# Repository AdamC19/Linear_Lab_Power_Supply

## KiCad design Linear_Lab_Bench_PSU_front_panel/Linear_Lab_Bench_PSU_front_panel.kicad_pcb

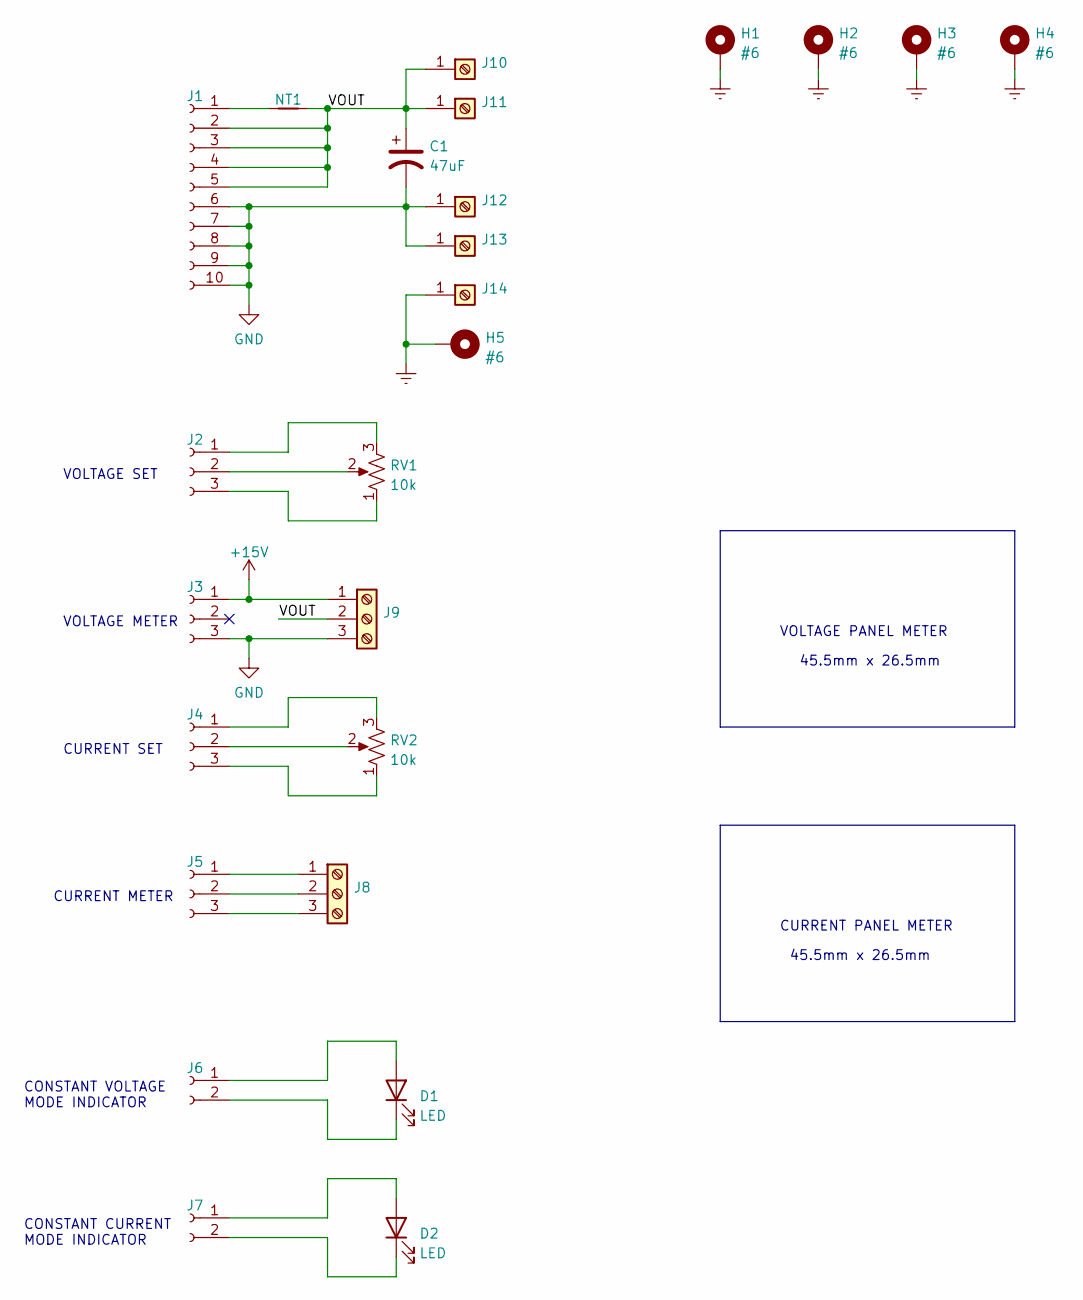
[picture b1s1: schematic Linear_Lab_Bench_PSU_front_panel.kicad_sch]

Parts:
C1: 47uF; CP_Radial_D8.0mm_P3.50mm
D1, D2: LED; LED_D5.0mm
H1, H2, H3, H4, H5: #6; MountingHole_3.7mm_Pad
J1: Conn_01x10_Female; PinSocket_1x10_P2.54mm_Vertical
J2, J3, J4, J5: Conn_01x03_Female; PinSocket_1x03_P2.54mm_Vertical
J6, J7: Conn_01x02_Female; PinSocket_1x02_P2.54mm_Vertical
J8, J9: Screw_Terminal_01x03; PhoenixContact_MCV_1,5_3-G-3.81_1x03_P3.81mm_Vertical
J10, J11, J12, J13, J14: Screw_Terminal_01x01; MountingHole_5.3mm_M5_Pad_Via
NT1: NetTie_2; NetTie-2_SMD_Pad0.5mm
RV1, RV2: 10k; Pot_TT_P160KNPD-4FC

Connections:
+15V: J3.1, J9.1
/VOUT: C1.1, J1.2, J1.3, J1.4, J1.5, J9.2, J10.1, J11.1, NT1.2
Earth: H1.1, H2.1, H3.1, H4.1, H5.1, J14.1
GND: C1.2, J1.6, J1.7, J1.8, J1.9, J1.10, J3.3, J9.3, J12.1, J13.1
unnamed: D1.1 (K), J6.2
unnamed: D1.2 (A), J6.1
unnamed: D2.1 (K), J7.2
unnamed: D2.2 (A), J7.1
unnamed: J1.1, NT1.1
unnamed: J2.1, RV1.3
unnamed: J2.2, RV1.2
unnamed: J2.3, RV1.1
unnamed: J4.1, RV2.3
unnamed: J4.2, RV2.2
unnamed: J4.3, RV2.1
unnamed: J5.1, J8.1
unnamed: J5.2, J8.2
unnamed: J5.3, J8.3

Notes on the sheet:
45.5mm x 26.5mm
VOLTAGE METER
CURRENT PANEL METER
CURRENT METER
VOLTAGE PANEL METER
CONSTANT CURRENT MODE INDICATOR
CURRENT SET
VOLTAGE SET
CONSTANT VOLTAGE MODE INDICATOR

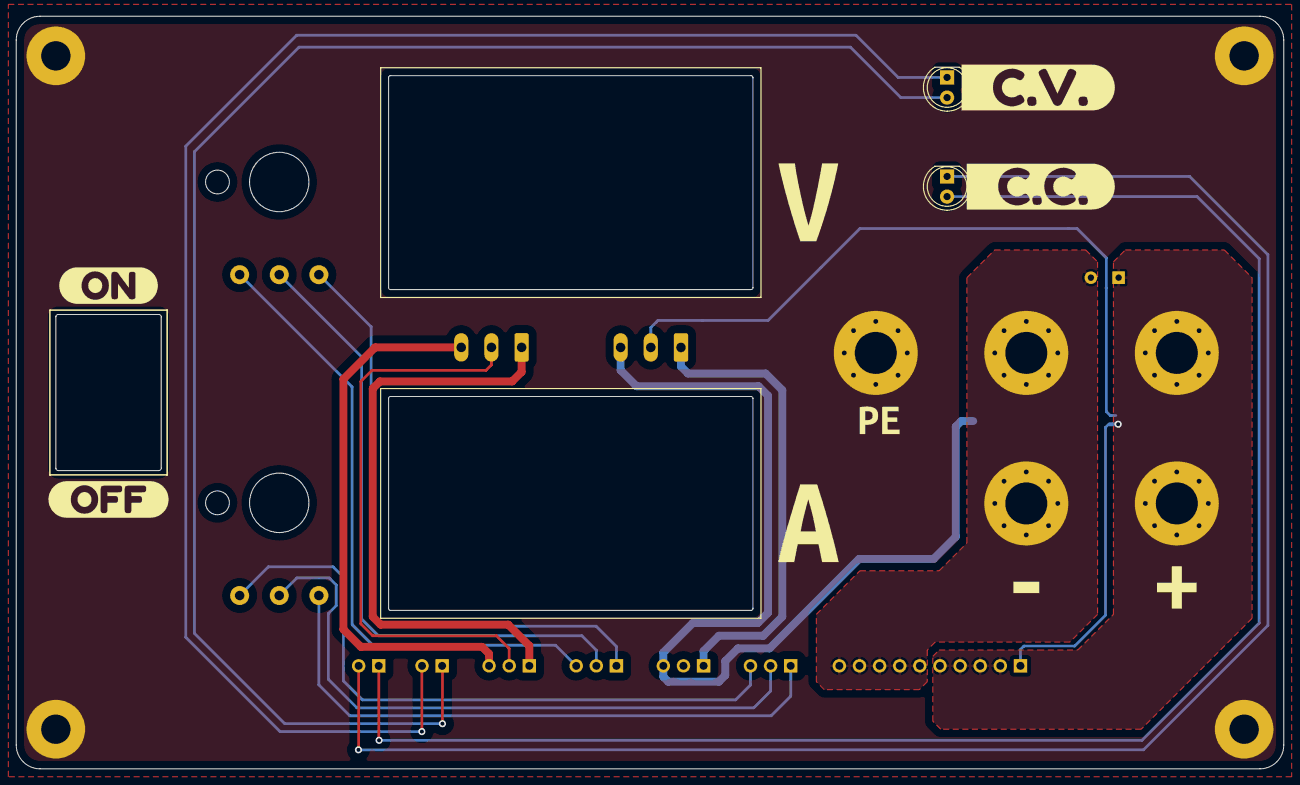
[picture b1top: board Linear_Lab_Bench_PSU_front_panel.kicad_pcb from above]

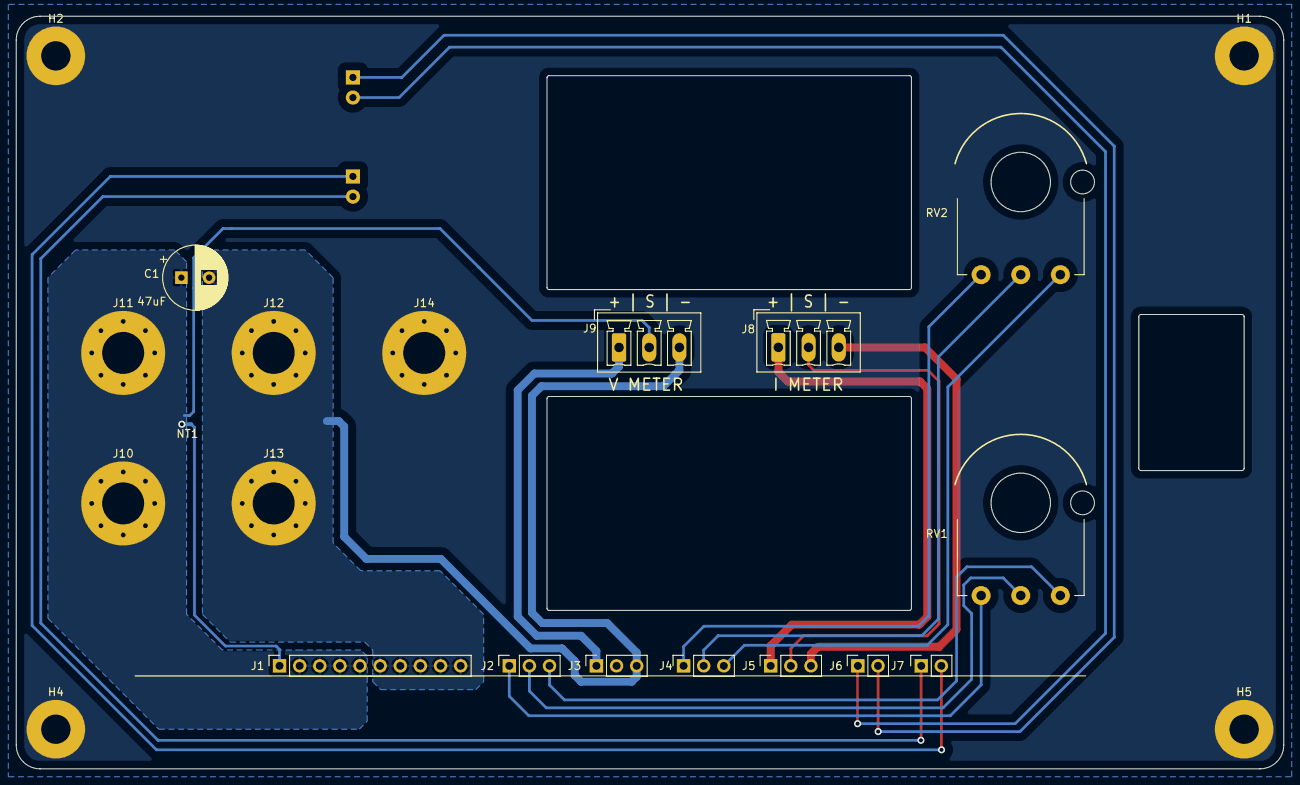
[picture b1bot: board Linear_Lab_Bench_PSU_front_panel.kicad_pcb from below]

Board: 2 copper layers, 160.0 x 95.0 mm, 33 parts (22 on the bottom side), 18 nets.

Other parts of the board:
kibuzzard-6225A7BC: G***; kibuzzard-6225A7BC
kibuzzard-6225A7C7: G***; kibuzzard-6225A7C7
kibuzzard-6225A77E: G***; kibuzzard-6225A77E
kibuzzard-6225A745: G***; kibuzzard-6225A745
kibuzzard-6225A755: G***; kibuzzard-6225A755
kibuzzard-62263B3C: G***; kibuzzard-62263B3C
kibuzzard-62263B33: G***; kibuzzard-62263B33
kibuzzard-62263C4A: G***; kibuzzard-62263C4A
kibuzzard-62263C42: G***; kibuzzard-62263C42

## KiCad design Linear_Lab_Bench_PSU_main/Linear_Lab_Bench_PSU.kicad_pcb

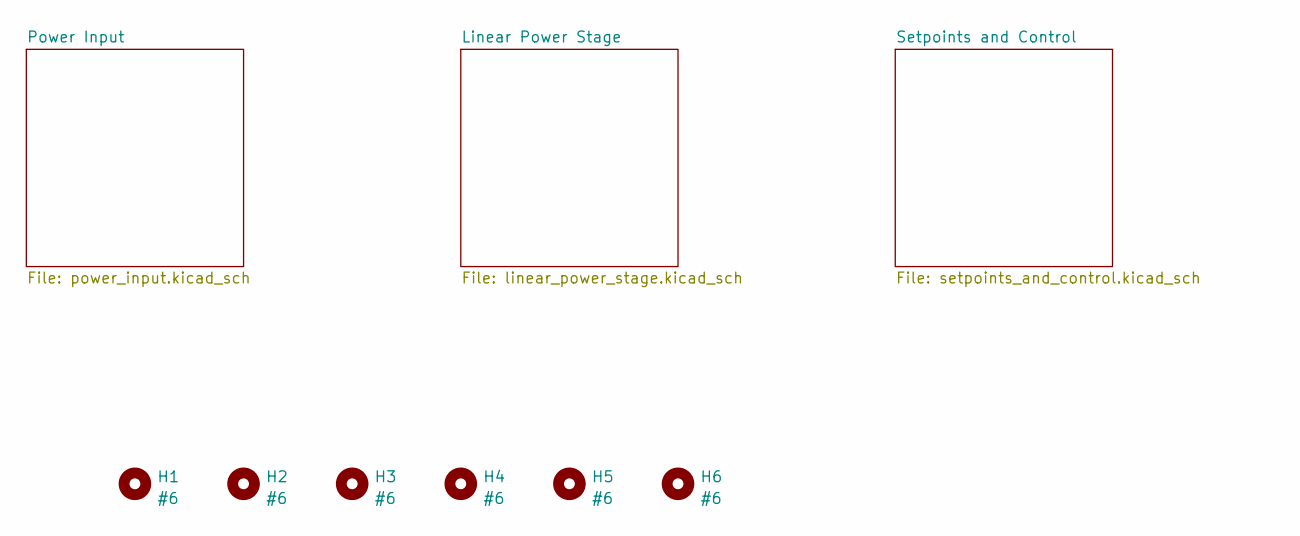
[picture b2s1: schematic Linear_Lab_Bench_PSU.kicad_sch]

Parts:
H1, H2, H3, H4, H5, H6: #6; MountingHole_3.7mm_Pad

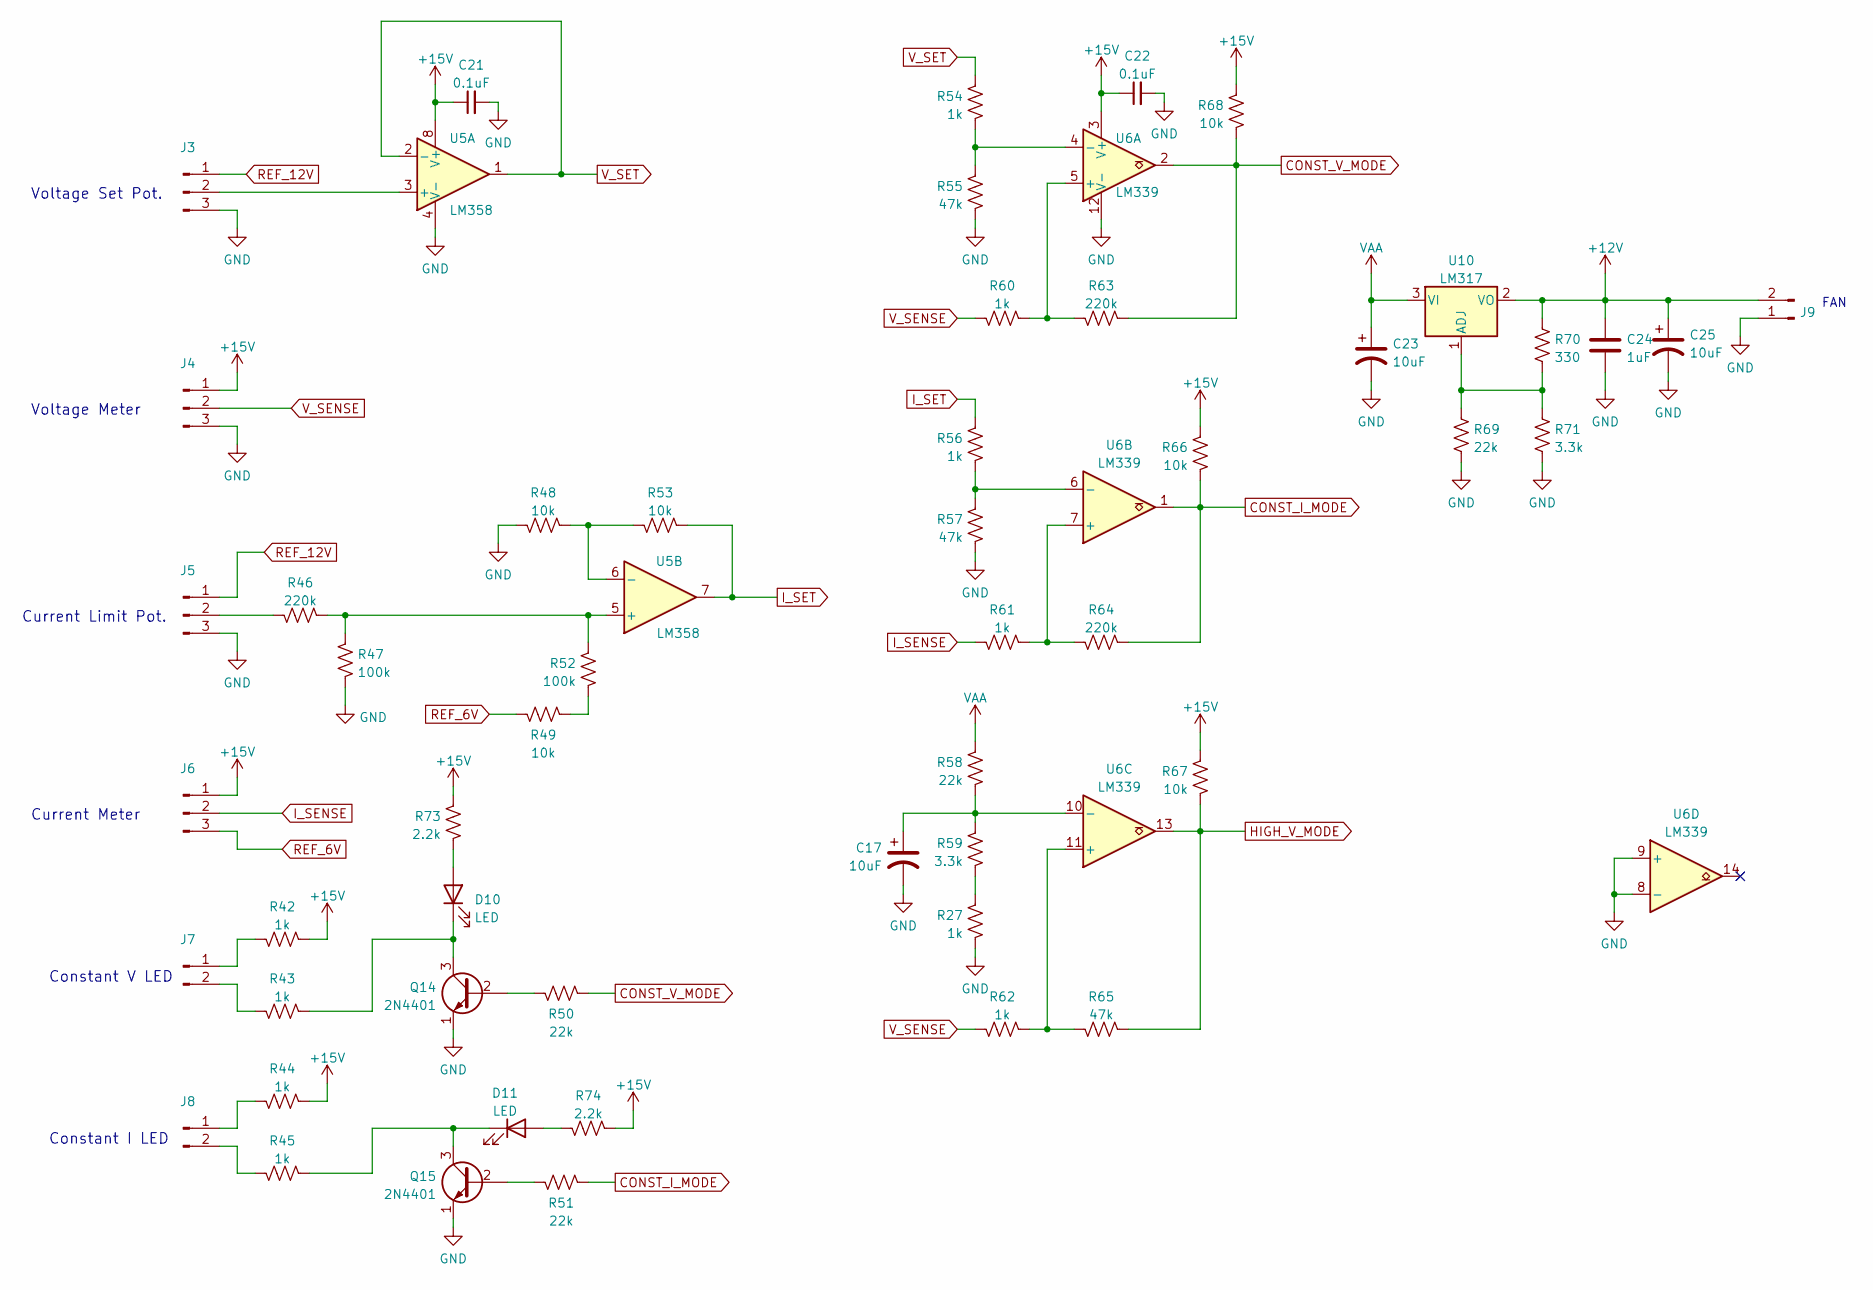
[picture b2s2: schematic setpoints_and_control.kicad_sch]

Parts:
C17, C23, C25: 10uF; CP_Radial_D5.0mm_P2.50mm
C21, C22: 0.1uF; C_Disc_D5.0mm_W2.5mm_P2.50mm
C24: 1uF; C_Axial_L5.1mm_D3.1mm_P7.50mm_Horizontal
D10, D11: LED; LED_D5.0mm
J3, J4, J5, J6: Conn_01x03_Male; PinHeader_1x03_P2.54mm_Horizontal
J7, J8: Conn_01x02_Male; PinHeader_1x02_P2.54mm_Horizontal
J9: Conn_01x02_Male; PinHeader_1x02_P2.54mm_Vertical
Q14, Q15: 2N4401; TO-92_Inline_Wide
R27, R42, R43, R44, R45, R54, R56, R60, R61, R62: 1k; R_Axial_DIN0207_L6.3mm_D2.5mm_P10.16mm_Horizontal
R46, R63, R64: 220k; R_Axial_DIN0207_L6.3mm_D2.5mm_P10.16mm_Horizontal
R47, R52: 100k; R_Axial_DIN0207_L6.3mm_D2.5mm_P10.16mm_Horizontal
R48, R49, R53, R66, R67, R68: 10k; R_Axial_DIN0207_L6.3mm_D2.5mm_P10.16mm_Horizontal
R50, R51, R58, R69: 22k; R_Axial_DIN0207_L6.3mm_D2.5mm_P10.16mm_Horizontal
R55, R57, R65: 47k; R_Axial_DIN0207_L6.3mm_D2.5mm_P10.16mm_Horizontal
R59, R71: 3.3k; R_Axial_DIN0207_L6.3mm_D2.5mm_P10.16mm_Horizontal
R70: 330; R_Axial_DIN0207_L6.3mm_D2.5mm_P10.16mm_Horizontal
R73, R74: 2.2k; R_Axial_DIN0207_L6.3mm_D2.5mm_P10.16mm_Horizontal
U5: LM358; DIP-8_W7.62mm
U6: LM339; DIP-14_W7.62mm
U10: LM317; TO-220-3_Vertical

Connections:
+12V: C24.1, C25.1, J9.2, R70.1, U10.2 (VO)
+15V: C21.1, C22.1, J4.1, J6.1, R42.2, R44.2, R66.2, R67.2, R68.2, R73.2, R74.2, U5.8 (V+), U6.3 (V+); also elsewhere on the board
CONST_I_MODE: R51.1, R64.2, R66.1, U6.1
CONST_V_MODE: R50.1, R63.2, R68.1, U6.2
GND: C17.2, C21.2, C22.2, C23.2, C24.2, C25.2, J3.3, J4.3, J5.3, J9.1, Q14.1 (E), Q15.1 (E), R27.1, R47.2, R48.1, R55.1, R57.1, R69.2, R71.2, U5.4 (V-), U6.8 (-), U6.9 (+), U6.12 (V-); also elsewhere on the board
HIGH_V_MODE: R65.2, R67.1, U6.13; also elsewhere on the board
I_SENSE: J6.2, R61.2; also elsewhere on the board
I_SET: R53.2, R56.2, U5.7; also elsewhere on the board
unnamed: C17.1, R58.1, R59.2, U6.10 (-)
unnamed: D10.1 (K), Q14.3 (C), R43.2
unnamed: D10.2 (A), R73.1
unnamed: D11.1 (K), Q15.3 (C), R45.2
unnamed: D11.2 (A), R74.1
unnamed: J3.2, U5.3 (+)
unnamed: J5.2, R46.2
unnamed: J7.1, R42.1
unnamed: J7.2, R43.1
unnamed: J8.1, R44.1
unnamed: J8.2, R45.1
unnamed: Q14.2 (B), R50.2
unnamed: Q15.2 (B), R51.2
unnamed: R27.2, R59.1
unnamed: R46.1, R47.1, R52.2, U5.5 (+)
unnamed: R48.2, R53.1, U5.6 (-)
unnamed: R49.1, R52.1
unnamed: R54.1, R55.2, U6.4 (-)
unnamed: R56.1, R57.2, U6.6 (-)
unnamed: R60.1, R63.1, U6.5 (+)
unnamed: R61.1, R64.1, U6.7 (+)
unnamed: R62.1, R65.1, U6.11 (+)
unnamed: R69.1, R70.2, R71.1, U10.1 (ADJ)
REF_6V: J6.3, R49.2; also elsewhere on the board
REF_12V: J3.1, J5.1; also elsewhere on the board
VAA: C23.1, R58.2, U10.3 (VI); also elsewhere on the board
V_SENSE: J4.2, R60.2, R62.2; also elsewhere on the board
V_SET: R54.2, U5.1, U5.2 (-); also elsewhere on the board

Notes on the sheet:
Constant I LED
Voltage Meter
Constant V LED
Voltage Set Pot.
FAN
Current Limit Pot.
Current Meter

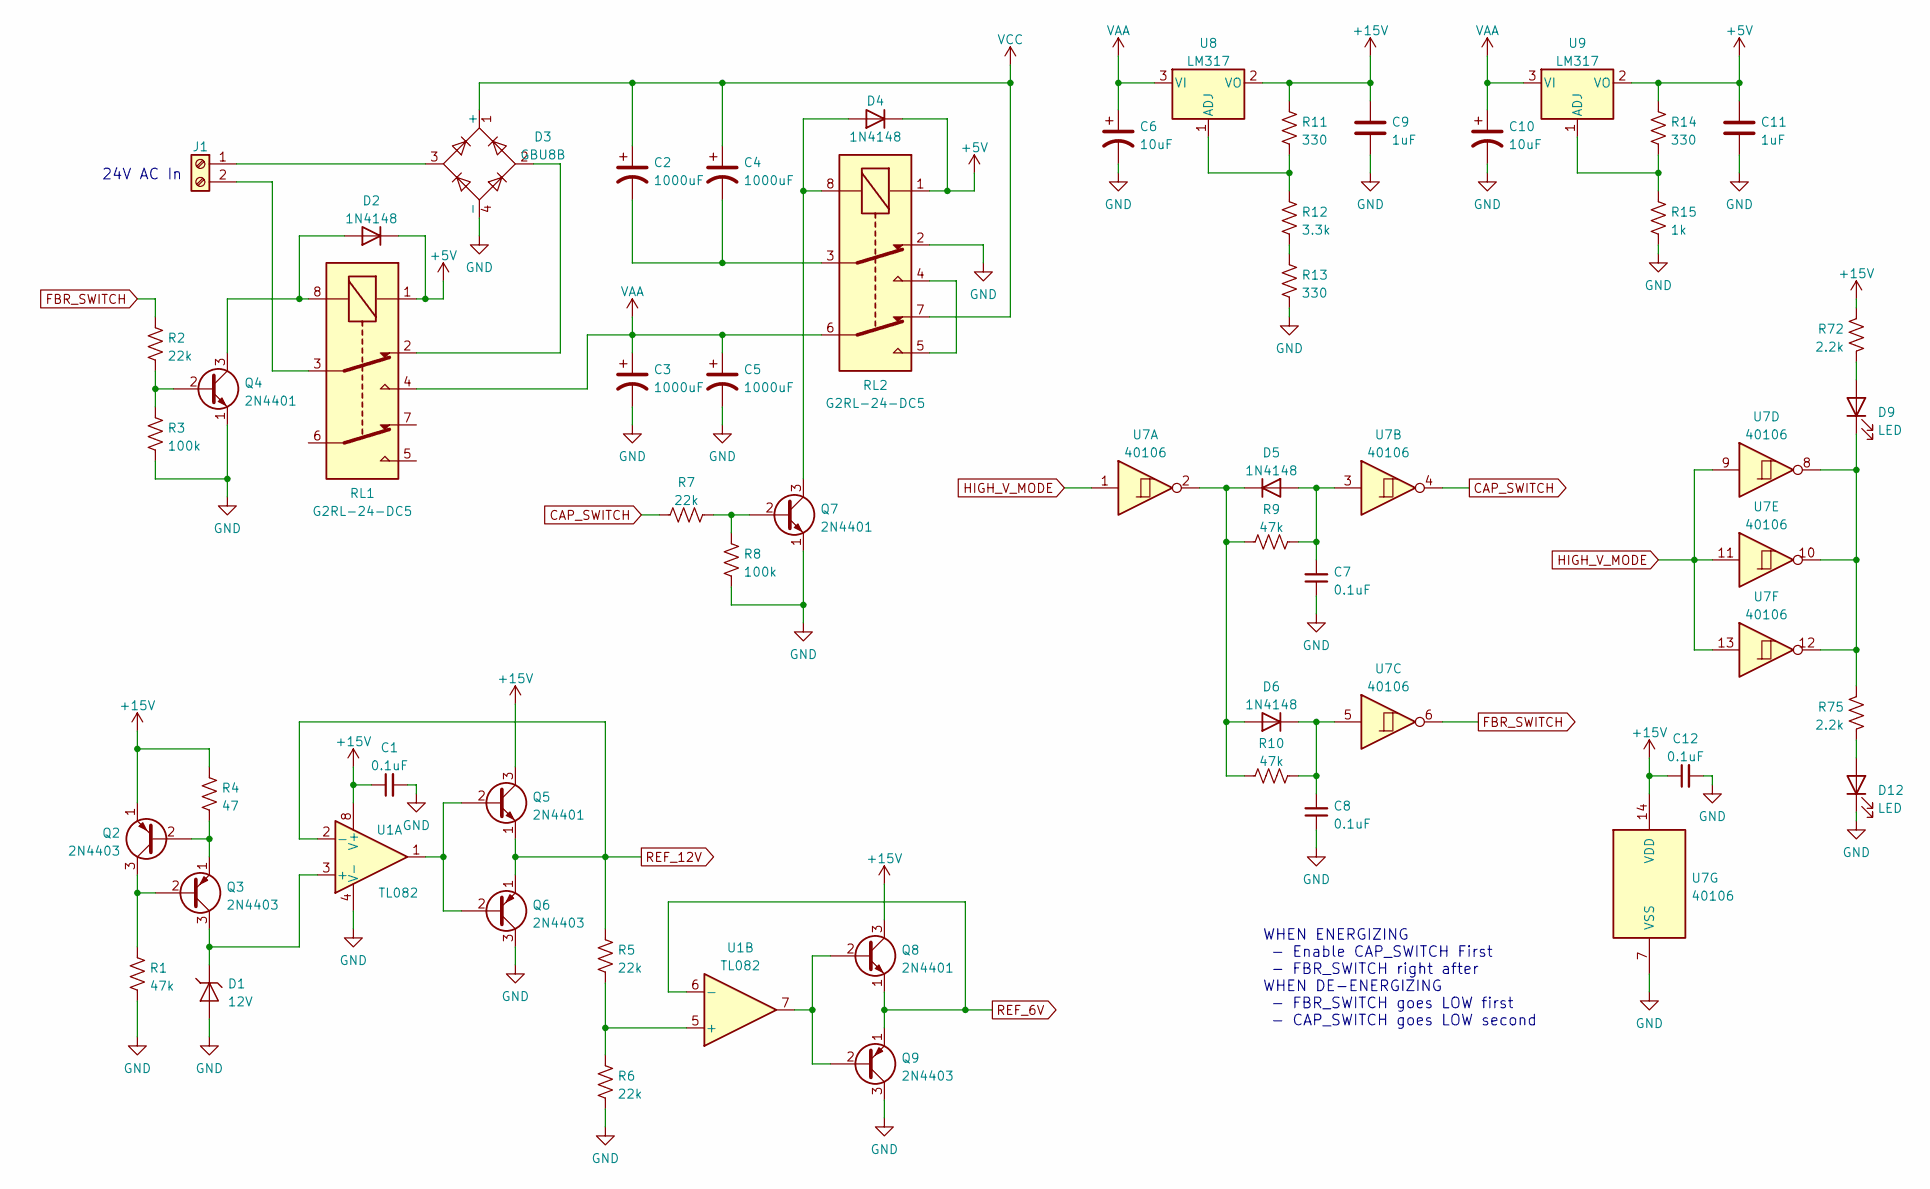
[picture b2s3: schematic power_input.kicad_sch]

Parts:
C1, C7, C8, C12: 0.1uF; C_Disc_D5.0mm_W2.5mm_P2.50mm
C2: 1000uF; CP_Radial_D16.0mm_P7.50mm; MFG_PN EKY-500ELL102ML25S
C3, C4, C5: 1000uF; CP_Radial_D16.0mm_P7.50mm
C6, C10: 10uF; CP_Radial_D5.0mm_P2.50mm
C9, C11: 1uF; C_Axial_L5.1mm_D3.1mm_P7.50mm_Horizontal
D1: 12V; D_DO-41_SOD81_P10.16mm_Horizontal
D2, D4, D5, D6: 1N4148; D_DO-35_SOD27_P7.62mm_Horizontal
D3: GBU8B; Diode_Bridge_Vishay_GBU
D9, D12: LED; LED_D5.0mm
J1: Screw_Terminal_01x02; PhoenixContact_GMSTBA_2,5_2-G-7,62_1x02_P7.62mm_Horizontal
Q2, Q3, Q6, Q9: 2N4403; TO-92_Inline_Wide
Q4, Q5, Q7, Q8: 2N4401; TO-92_Inline_Wide
R1, R9, R10: 47k; R_Axial_DIN0207_L6.3mm_D2.5mm_P10.16mm_Horizontal
R2, R5, R6, R7: 22k; R_Axial_DIN0207_L6.3mm_D2.5mm_P10.16mm_Horizontal
R3, R8: 100k; R_Axial_DIN0207_L6.3mm_D2.5mm_P10.16mm_Horizontal
R4: 47; R_Axial_DIN0207_L6.3mm_D2.5mm_P10.16mm_Horizontal
R11, R13, R14: 330; R_Axial_DIN0207_L6.3mm_D2.5mm_P10.16mm_Horizontal
R12: 3.3k; R_Axial_DIN0207_L6.3mm_D2.5mm_P10.16mm_Horizontal
R15: 1k; R_Axial_DIN0207_L6.3mm_D2.5mm_P10.16mm_Horizontal
R72, R75: 2.2k; R_Axial_DIN0207_L6.3mm_D2.5mm_P10.16mm_Horizontal
RL1, RL2: G2RL-24-DC5; Relay_DPDT_Omron_G2RL
U1: TL082; DIP-8_W7.62mm
U7: 40106; DIP-14_W7.62mm
U8, U9: LM317; TO-220-3_Vertical

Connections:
+5V: C11.1, D2.1 (K), D4.1 (K), R14.1, RL1.1, RL2.1, U9.2 (VO)
+15V: C1.1, C9.1, C12.1, Q2.1 (E), Q5.3 (C), Q8.3 (C), R4.1, R11.1, R72.2, U1.8 (V+), U7.14 (VDD), U8.2 (VO); also elsewhere on the board
CAP_SWITCH: R7.2, U7.4
FBR_SWITCH: R2.2, U7.6
GND: C1.2, C3.2, C5.2, C6.2, C7.1, C8.1, C9.2, C10.2, C11.2, C12.2, D1.2 (A), D3.4 (-), D12.1 (K), Q4.1 (E), Q6.3 (C), Q7.1 (E), Q9.3 (C), R1.2, R3.1, R6.2, R8.1, R13.2, R15.2, RL2.2, U1.4 (V-), U7.7 (VSS); also elsewhere on the board
HIGH_V_MODE: U7.1, U7.9, U7.11, U7.13; also elsewhere on the board
unnamed: C2.2, C4.2, RL2.3
unnamed: C7.2, D5.2 (A), R9.2, U7.3
unnamed: C8.2, D6.1 (K), R10.2, U7.5
unnamed: D1.1 (K), Q3.3 (C), U1.3 (+)
unnamed: D2.2 (A), Q4.3 (C), RL1.8
unnamed: D3.2, RL1.2
unnamed: D3.3, J1.1
unnamed: D4.2 (A), Q7.3 (C), RL2.8
unnamed: D5.1 (K), D6.2 (A), R9.1, R10.1, U7.2
unnamed: D9.1 (K), R75.2, U7.8, U7.10, U7.12
unnamed: D9.2 (A), R72.1
unnamed: D12.2 (A), R75.1
unnamed: J1.2, RL1.3
unnamed: Q2.2 (B), Q3.1 (E), R4.2
unnamed: Q2.3 (C), Q3.2 (B), R1.1
unnamed: Q4.2 (B), R2.1, R3.2
unnamed: Q5.2 (B), Q6.2 (B), U1.1
unnamed: Q7.2 (B), R7.1, R8.2
unnamed: Q8.2 (B), Q9.2 (B), U1.7
unnamed: R5.2, R6.1, U1.5 (+)
unnamed: R11.2, R12.1, U8.1 (ADJ)
unnamed: R12.2, R13.1
unnamed: R14.2, R15.1, U9.1 (ADJ)
unnamed: RL2.4, RL2.5
REF_6V: Q8.1 (E), Q9.1 (E), U1.6 (-); also elsewhere on the board
REF_12V: Q5.1 (E), Q6.1 (E), R5.1, U1.2 (-); also elsewhere on the board
VAA: C3.1, C5.1, C6.1, C10.1, RL1.4, RL2.6, U8.3 (VI), U9.3 (VI); also elsewhere on the board
VCC: C2.1, C4.1, D3.1 (+), RL2.7; also elsewhere on the board

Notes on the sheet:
WHEN ENERGIZING - Enable CAP_SWITCH First - FBR_SWITCH right after WHEN DE-ENERGIZING - FBR_SWITCH goes LOW first - CAP_SWITCH goes LOW second
24V AC In

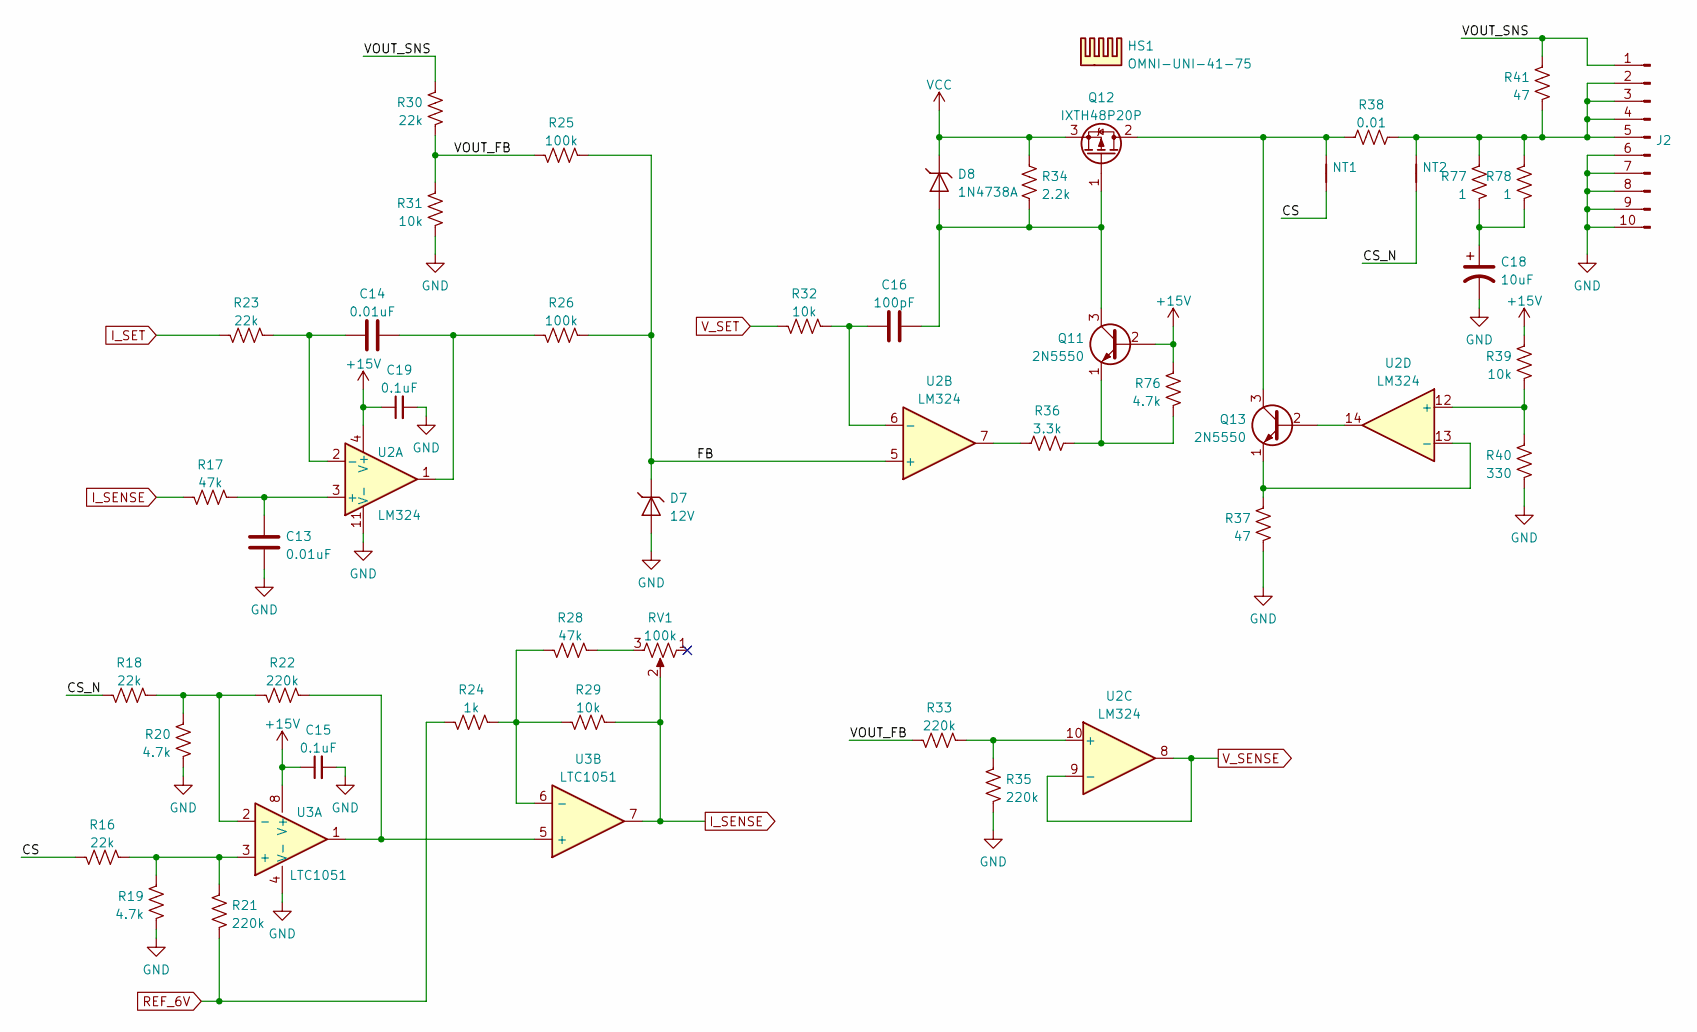
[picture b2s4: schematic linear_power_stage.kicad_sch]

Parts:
C13, C14: 0.01uF; C_Disc_D7.0mm_W2.5mm_P5.00mm
C15, C19: 0.1uF; C_Disc_D5.0mm_W2.5mm_P2.50mm
C16: 100pF; C_Disc_D5.0mm_W2.5mm_P2.50mm
C18: 10uF; CP_Radial_D5.0mm_P2.50mm
D7: 12V; D_DO-41_SOD81_P10.16mm_Horizontal
D8: 1N4738A; D_DO-41_SOD81_P10.16mm_Horizontal
HS1: OMNI-UNI-41-75; Wakefield_Vette_OMNI-UNI-41-75
J2: Conn_01x10_Male; PinHeader_1x10_P2.54mm_Horizontal
NT1, NT2: NetTie_2; NetTie-2_SMD_Pad0.5mm
Q11, Q13: 2N5550; TO-92_Inline_Wide
Q12: IXTH48P20P; TO-247-3_Vertical
R16, R18, R23, R30: 22k; R_Axial_DIN0207_L6.3mm_D2.5mm_P10.16mm_Horizontal
R17, R28: 47k; R_Axial_DIN0207_L6.3mm_D2.5mm_P10.16mm_Horizontal
R19, R20, R76: 4.7k; R_Axial_DIN0207_L6.3mm_D2.5mm_P10.16mm_Horizontal
R21, R22, R33, R35: 220k; R_Axial_DIN0207_L6.3mm_D2.5mm_P10.16mm_Horizontal
R24: 1k; R_Axial_DIN0207_L6.3mm_D2.5mm_P10.16mm_Horizontal
R25, R26: 100k; R_Axial_DIN0207_L6.3mm_D2.5mm_P10.16mm_Horizontal
R29, R31, R32, R39: 10k; R_Axial_DIN0207_L6.3mm_D2.5mm_P10.16mm_Horizontal
R34: 2.2k; R_Axial_DIN0207_L6.3mm_D2.5mm_P10.16mm_Horizontal
R36: 3.3k; R_Axial_DIN0207_L6.3mm_D2.5mm_P10.16mm_Horizontal
R37, R41: 47; R_Axial_DIN0207_L6.3mm_D2.5mm_P10.16mm_Horizontal
R38: 0.01; R_Bare_Metal_Element_L16.3mm_W4.8mm_P15.30mm; MFG_PN BR3FB10L0
R40: 330; R_Axial_DIN0207_L6.3mm_D2.5mm_P10.16mm_Horizontal
R77, R78: 1; R_Axial_DIN0207_L6.3mm_D2.5mm_P10.16mm_Horizontal
RV1: 100k; Potentiometer_Bourns_3386P_Vertical
U2: LM324; DIP-14_W7.62mm
U3: LTC1051; DIP-8_W7.62mm

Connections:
+15V: C15.1, C19.1, Q11.2 (B), R39.2, R76.2, U2.4 (V+), U3.8 (V+); also elsewhere on the board
/Linear Power Stage/CS: NT1.1, R16.2
/Linear Power Stage/CS_N: NT2.1, R18.2
/Linear Power Stage/FB: D7.1 (K), R25.1, R26.1, U2.5 (+)
/Linear Power Stage/VOUT_FB: R25.2, R30.1, R31.2, R33.2
/Linear Power Stage/VOUT_SNS: J2.1, R30.2, R41.1
GND: C13.2, C15.2, C18.2, C19.2, D7.2 (A), J2.6, J2.7, J2.8, J2.9, J2.10, R19.1, R20.1, R31.1, R35.2, R37.2, R40.1, U2.11 (V-), U3.4 (V-); also elsewhere on the board
I_SENSE: R17.2, R29.1, RV1.2, U3.7; also elsewhere on the board
I_SET: R23.2; also elsewhere on the board
unnamed: C13.1, R17.1, U2.3 (+)
unnamed: C14.1, R23.1, U2.2 (-)
unnamed: C14.2, R26.2, U2.1
unnamed: C16.1, R32.1, U2.6 (-)
unnamed: C16.2, D8.2 (A), Q11.3 (C), Q12.1 (G), R34.2
unnamed: C18.1, R77.2, R78.2
unnamed: J2.2, J2.3, J2.4, J2.5, NT2.2, R38.2, R41.2, R77.1, R78.1
unnamed: NT1.2, Q12.2 (D), Q13.3 (C), R38.1
unnamed: Q11.1 (E), R36.2, R76.1
unnamed: Q13.1 (E), R37.1, U2.13 (-)
unnamed: Q13.2 (B), U2.14
unnamed: R16.1, R19.2, R21.1, U3.3 (+)
unnamed: R18.1, R20.2, R22.2, U3.2 (-)
unnamed: R22.1, U3.1, U3.5 (+)
unnamed: R24.1, R28.2, R29.2, U3.6 (-)
unnamed: R28.1, RV1.3
unnamed: R33.1, R35.1, U2.10 (+)
unnamed: R36.1, U2.7
unnamed: R39.1, R40.2, U2.12 (+)
REF_6V: R21.2, R24.2; also elsewhere on the board
VCC: D8.1 (K), Q12.3 (S), R34.1; also elsewhere on the board
V_SENSE: U2.8, U2.9 (-); also elsewhere on the board
V_SET: R32.2; also elsewhere on the board

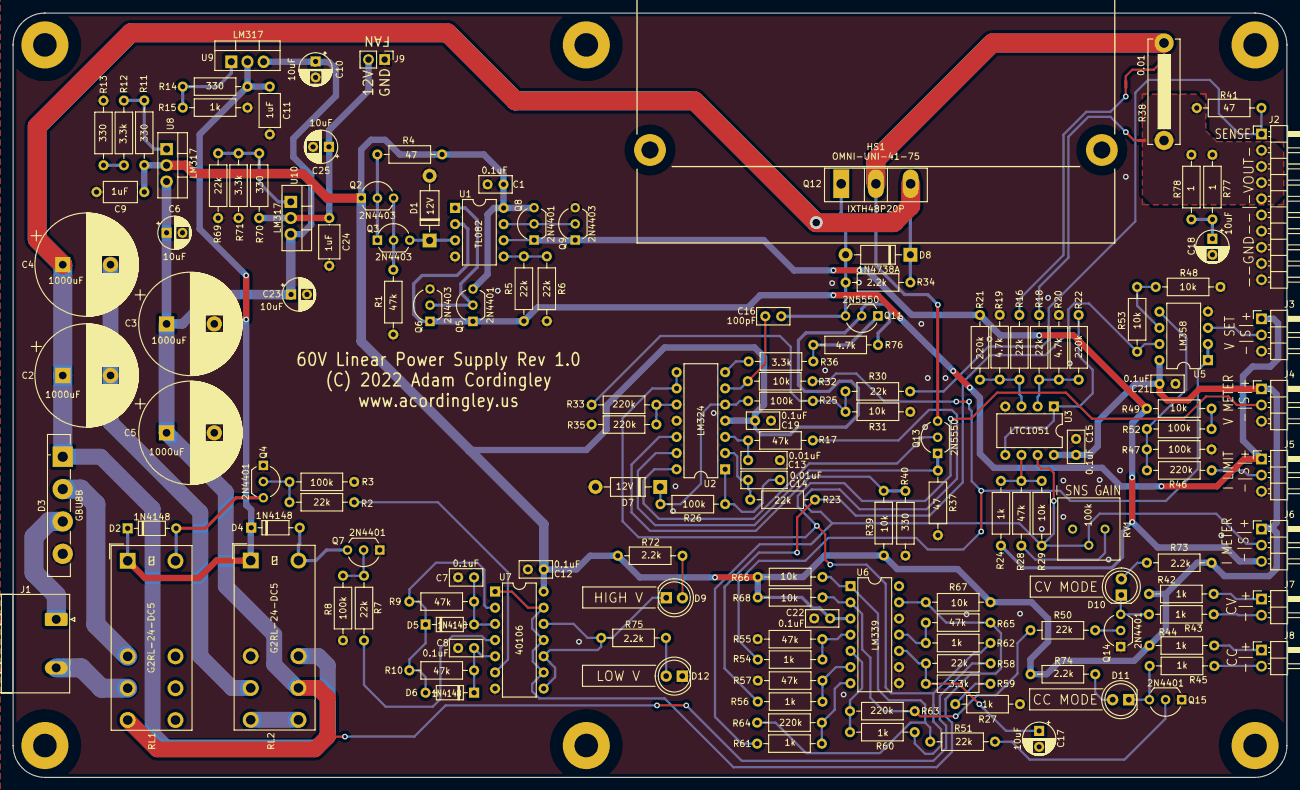
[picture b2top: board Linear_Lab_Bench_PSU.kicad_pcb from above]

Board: 2 copper layers, 200.0 x 120.0 mm, 157 parts (0 on the bottom side), 88 nets.

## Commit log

2022-03-09 Add 3D Models and STLs for case
2022-03-16 some basic concept code
2022-03-16 more basic stuff
2022-03-20 Notes on schematic for resistor changes

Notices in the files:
Linear_Lab_Bench_PSU_main/Linear_Lab_Bench_PSU.kicad_pcb:
(C) 2022 Adam Cordingley
